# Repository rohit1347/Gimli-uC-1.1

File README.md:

Improved version of Gimli, a Microcontroller Development Board based on ARM Cortex M4 microcontroller (Freescale MK22DX256VLF5).

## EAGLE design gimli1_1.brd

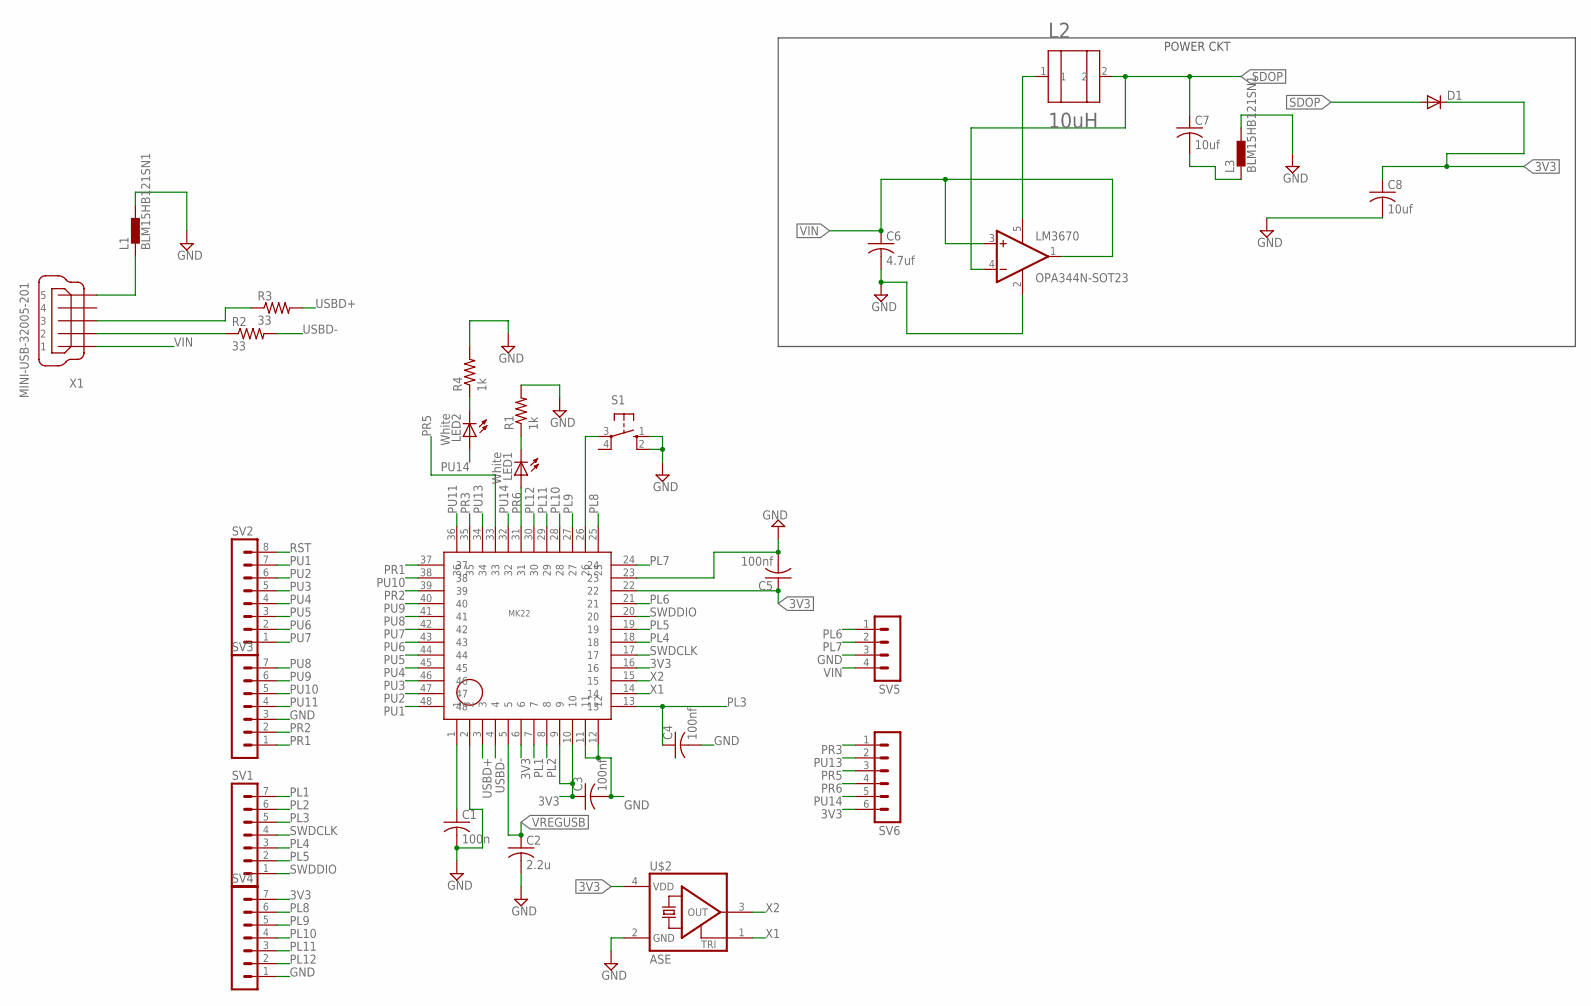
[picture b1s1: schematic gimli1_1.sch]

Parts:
C1: 100n; C0402
C2: 2.2u; C0402
C3, C4, C5: 100nf; C0402
C6: 4.7uf; C0402
C7, C8: 10uf; C0402
D1: DIODE-MICROMELF-W; MICROMELF-W
L1, L3: BLM15HB121SN1; 0402
L2: 10uH; INDUCTNEW
LED1, LED2: White; SML0603
LM3670: OPA344N-SOT23; SOT23-5
MK22: LQFP48
R1, R4: 1k; R0402
R2, R3: 33; R0402
S1: 10-XX; B3F-10XX
SV1, SV3, SV4: MA07-1
SV2: MA08-1
SV5: MA04-1
SV6: MA06-1
U$2: ASE
X1: MINI-USB-32005-201; 32005-201

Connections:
3V3: C3.1, C5.1, C8.1, D1.C, MK22.6, MK22.9, MK22.10, MK22.16, MK22.22, SV4.7, SV6.6, U$2.4 (VDD)
GND: C1.2, C2.2, C3.2, C4.2, C5.2, C6.2, C8.2, L1.1, L1.2, L3.2, LM3670.2 (V-), MK22.2, MK22.11, MK22.12, MK22.23, R1.2, R4.2, S1.1 (S), S1.2 (S1), SV3.3, SV4.1, SV5.3, U$2.2 (GND), X1.5
unnamed: C1.1, MK22.1
unnamed: C7.2, L3.1
unnamed: LED1.C, R1.1
unnamed: LED2.C, R4.1
unnamed: R2.1, X1.2
unnamed: R3.1, X1.3
unnamed: L2.1, LM3670.5 (V+)
PL1: MK22.7, SV1.7
PL2: MK22.8, SV1.6
PL3: C4.1, MK22.13, SV1.5
PL4: MK22.18, SV1.3
PL5: MK22.19, SV1.2
PL6: MK22.21, SV5.1
PL7: MK22.24, SV5.2
PL8: MK22.25, SV4.6
PL9: MK22.27, SV4.5
PL10: MK22.28, SV4.4
PL11: MK22.29, SV4.3
PL12: MK22.30, SV4.2
PR1: MK22.37, SV3.1
PR2: MK22.39, SV3.2
PR3: MK22.35, SV6.1
PR5: MK22.33, SV6.3
PR6: LED1.A, MK22.31, SV6.4
PU1: MK22.48, SV2.7
PU2: MK22.47, SV2.6
PU3: MK22.46, SV2.5
PU4: MK22.45, SV2.4
PU5: MK22.44, SV2.3
PU6: MK22.43, SV2.2
PU7: MK22.42, SV2.1
PU8: MK22.41, SV3.7
PU9: MK22.40, SV3.6
PU10: MK22.38, SV3.5
PU11: MK22.36, SV3.4
PU13: MK22.34, SV6.2
PU14: LED2.A, MK22.32, SV6.5
RST: MK22.26, S1.3, SV2.8
SDOP: C7.1, D1.A, L2.2, LM3670.4 (-IN)
SWDCLK: MK22.17, SV1.4
SWDDIO: MK22.20, SV1.1
USBD+: MK22.3, R3.2
USBD-: MK22.4, R2.2
VIN: C6.1, LM3670.1 (OUT), LM3670.3 (+IN), SV5.4, X1.1
VREGUSB: C2.1, MK22.5
X1: MK22.14, U$2.1 (TRI)
X2: MK22.15, U$2.3 (OUT)

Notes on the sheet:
POWER CKT

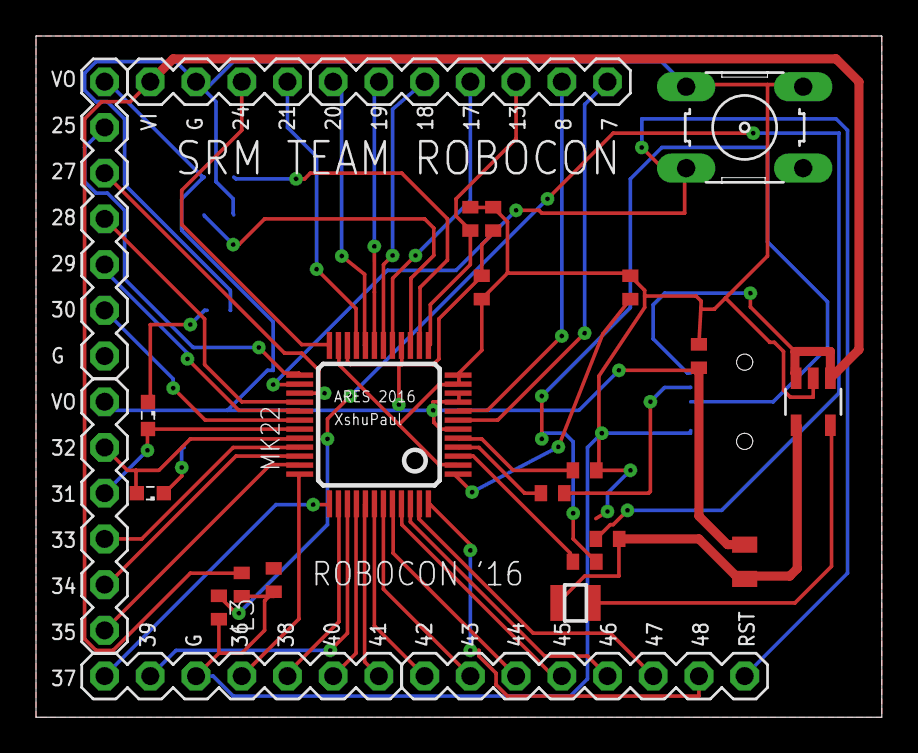
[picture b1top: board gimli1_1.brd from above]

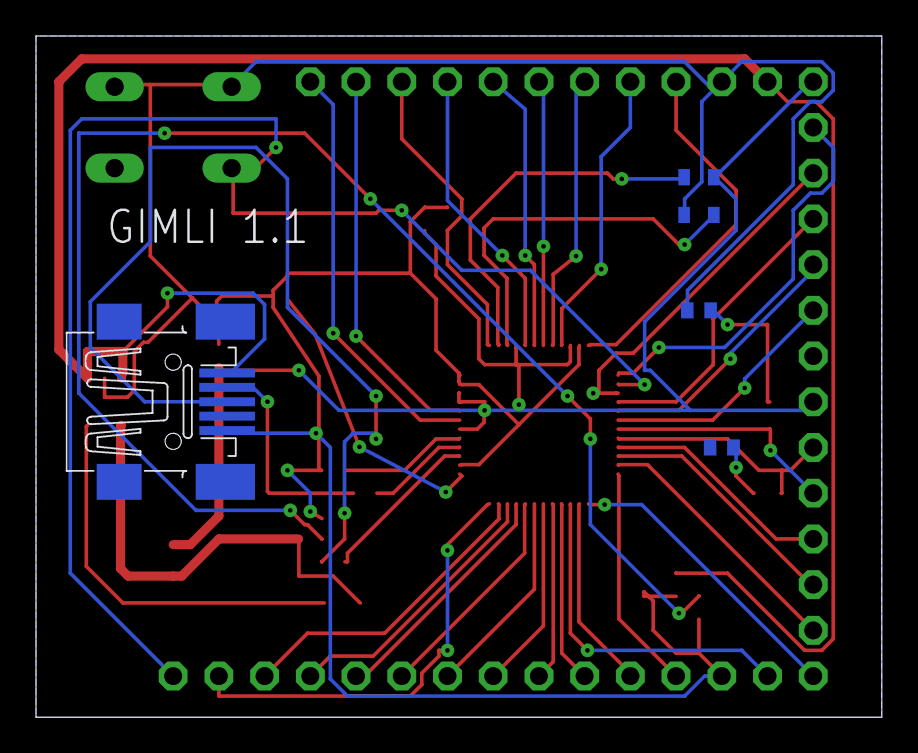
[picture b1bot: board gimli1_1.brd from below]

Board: 2 copper layers, 47.0 x 37.8 mm, 29 parts (4 on the bottom side), 49 nets.
